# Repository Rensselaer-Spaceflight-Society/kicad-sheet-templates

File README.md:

# KiCAD Drawing Sheet Template
Schematic and PCB layout drawing sheet templates for the Rensselaer Spaceflight Society's KiCAD Projects

## Features:
Extends the Default KiCAD drawing sheet to add the SFS logo and adds space for review comments and reviewer signoffs.

## How to use:

1. Download the drawing sheet file from this repository.
2. Create a new KiCAD project
3. Open the schematic editor
4. Double left click the bottom right corner of the drawing sheet
5. Use the file icon to select the drawing sheet

6. Fill in other necessary information, select OK.

7. Open the PCB editor
8. Double left click the bottom right corner of the drawing sheet
9. Use the file icon to select the drawing sheet

10. Fill in other necessary information, select OK.

## Adding Reviewers and Comments

To add review comments:

Double Left Click the bottom right corner of the drawing sheet. Then you can add comments from the dialog that pops up.
You can also use the text tool on the right hand side to add comments. If you are doing this in the PCB editor, select the "User.Comments" layer on the right hand side first.

To add reviewers: Use the text tool on the right hand side to add reviewers. If you are doing this in the PCB editor, select the "User.Comments" layer on the right hand side first.

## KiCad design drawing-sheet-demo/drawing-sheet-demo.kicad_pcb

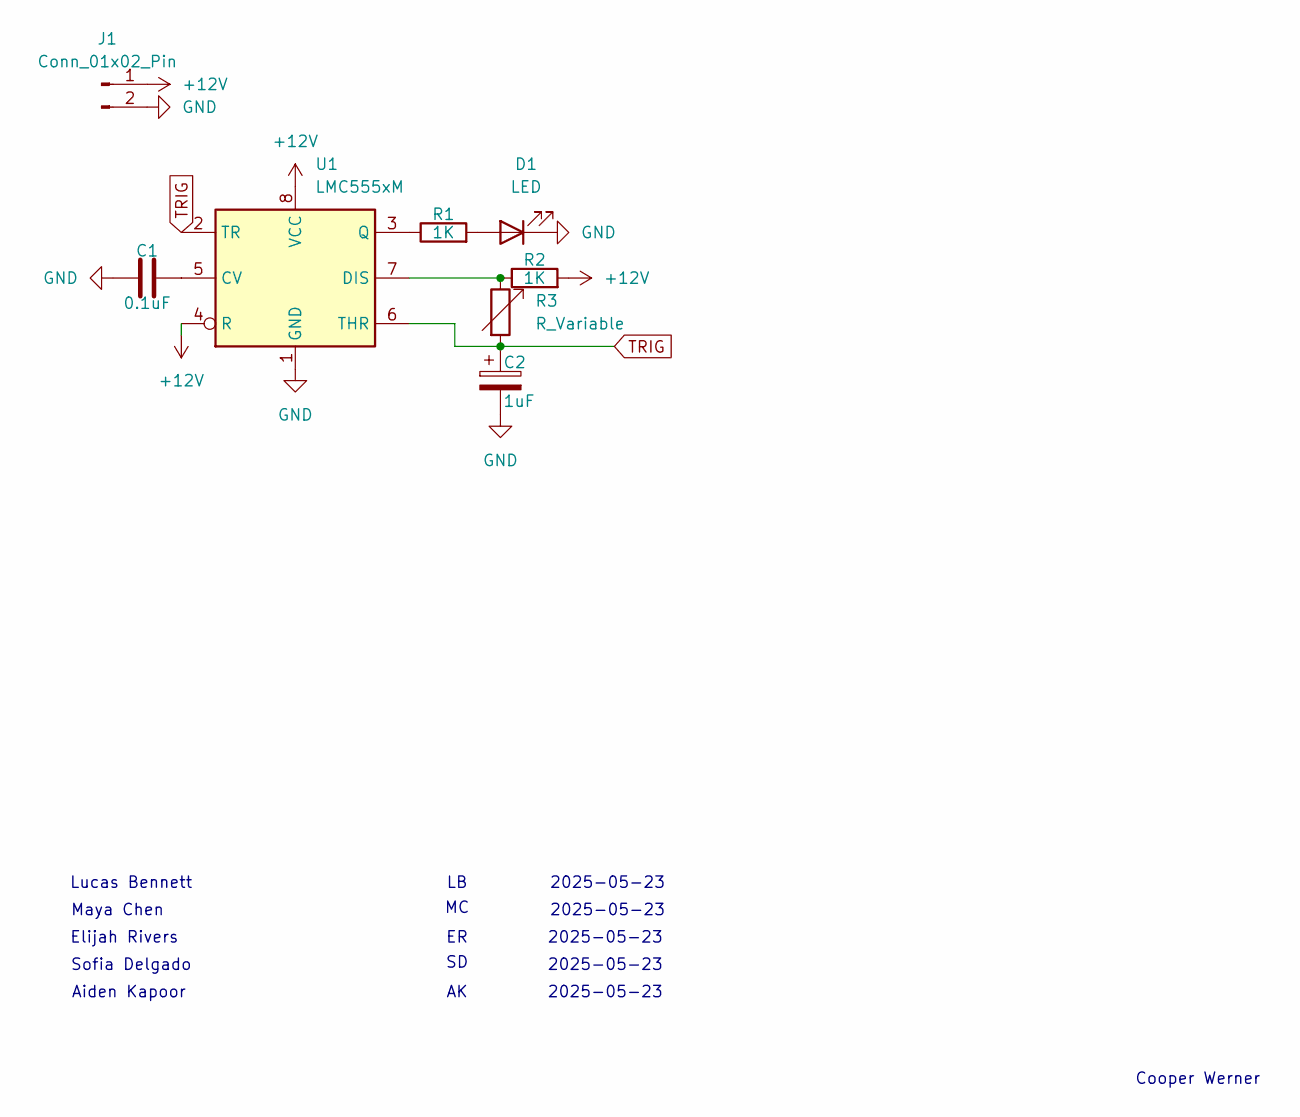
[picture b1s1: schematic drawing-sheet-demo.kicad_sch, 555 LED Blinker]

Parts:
C1: 0.1uF; C_0402_1005Metric
C2: 1uF; CP_Elec_4x4.5
D1: LED; LED_0402_1005Metric
J1: Conn_01x02_Pin; PinHeader_1x02_P2.54mm_Vertical
R1, R2: 1K; R_0402_1005Metric
R3: R_Variable; Potentiometer_Bourns_3386P_Vertical
U1: LMC555xM; SOIC-8_3.9x4.9mm_P1.27mm

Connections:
+12V: J1.1, R2.2, U1.4 (R), U1.8 (VCC)
GND: C1.1, C2.2, D1.1 (K), J1.2, U1.1 (GND)
unnamed: D1.2 (A), R1.2
unnamed: C1.2, U1.5 (CV)
unnamed: R2.1, R3.1, U1.7 (DIS)
unnamed: R1.1, U1.3 (Q)
TRIG: C2.1, R3.2, U1.2 (TR), U1.6 (THR)

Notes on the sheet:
2025-05-23
Aiden Kapoor
Lucas Bennett
Sofia Delgado
Maya Chen
Elijah Rivers
Cooper Werner

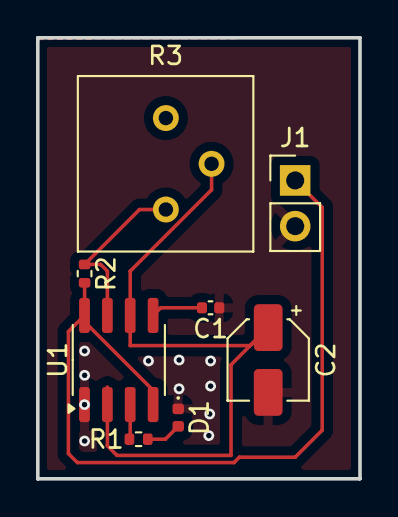
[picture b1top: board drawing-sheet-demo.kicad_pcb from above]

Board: 2 copper layers, 17.9 x 24.5 mm, 8 parts (0 on the bottom side), 7 nets.

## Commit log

2025-05-22 Add Drawing Sheet and Demo Project
2025-05-23 better match the Rocket Engine part review process
